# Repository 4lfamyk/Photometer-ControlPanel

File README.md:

# Raspberry-pi-photometer-controller
A control panel for photometer

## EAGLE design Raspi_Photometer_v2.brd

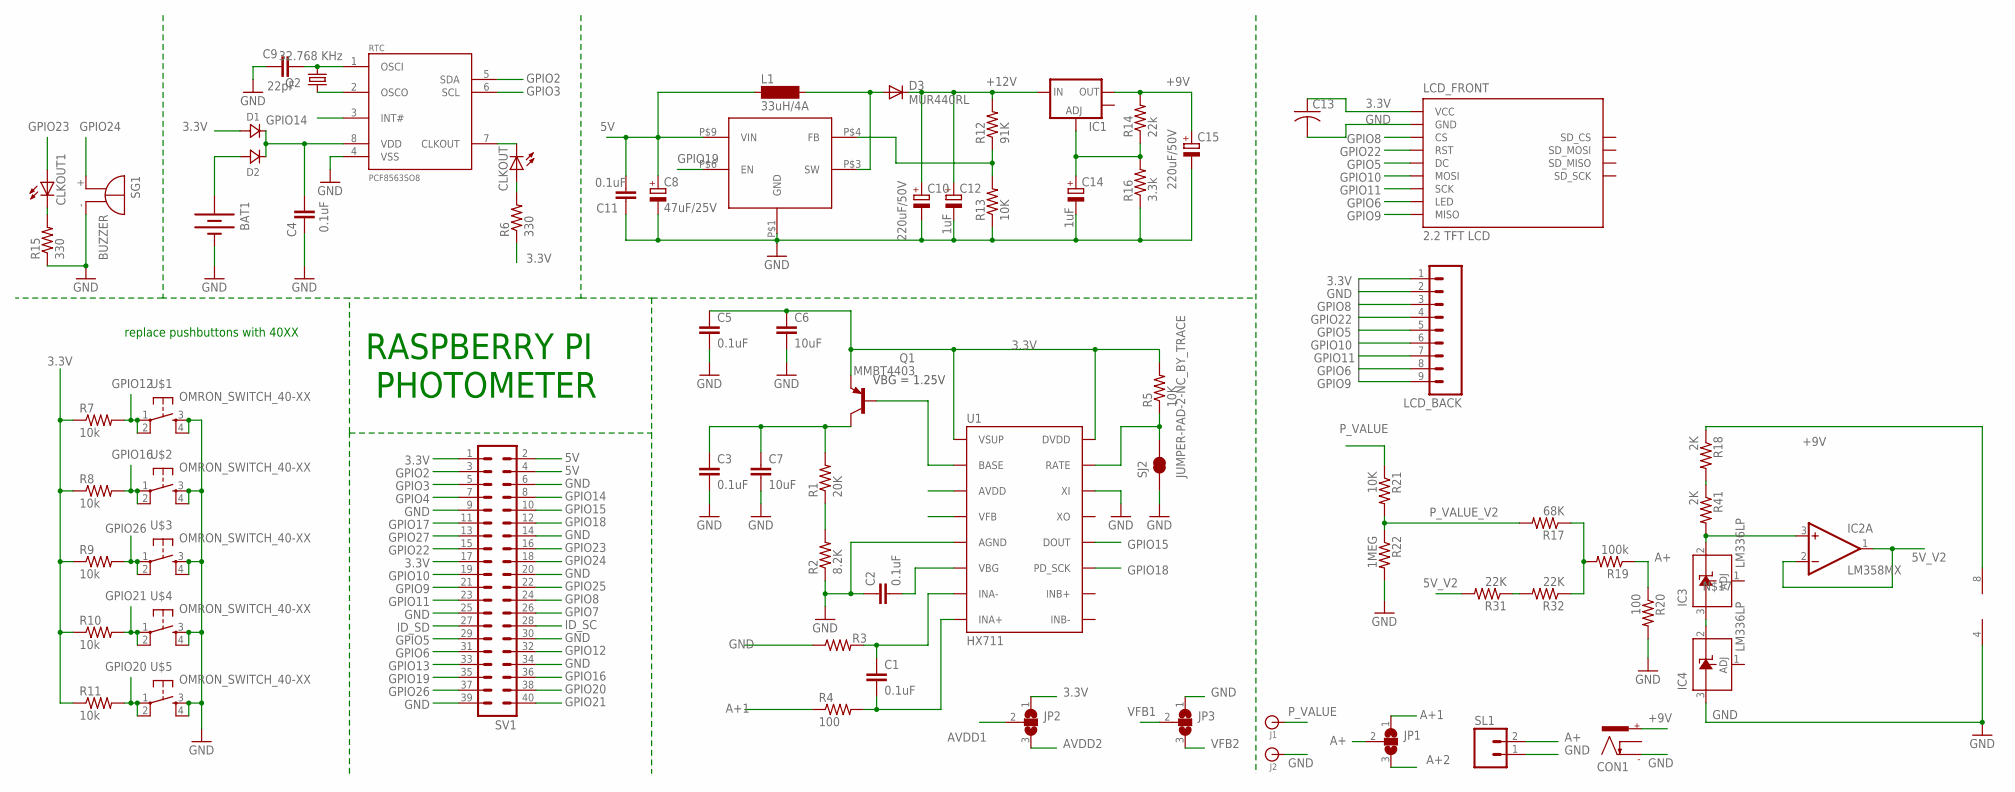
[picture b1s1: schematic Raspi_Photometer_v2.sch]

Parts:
BAT1: BATTERY20PTH; BATTCOM_20MM_PTH
C1, C2, C3, C5: 0.1uF; 0603-CAP
C4: 0.1uF; C0805K
C6, C7: 10uF; 1210
C8: 47uF/25V; E3,5-10
C9: 22pF; C0805K
C10, C15: 220uF/50V; E5-10,5
C11: 0.1uF; C0603
C12, C14: 1uF; E2,5-5
C13: C-USC0805; C0805
CLKOUT: LED0805; CHIPLED_0805
CLKOUT1: LED1206; CHIPLED_1206
CON1: POWER_CON; NEB21R
D1, D2: SS14; DO214
D3: MUR440RL; C2673
IC1: V_REG_LM1117SOT223; SOT223
IC2: LM358MX; SO08
IC3, IC4: LM336LP; TO92
J1, J2: BANANA_CONN
JP1, JP2, JP3: SJ2W; SJ_2
L1: 33uH/4A; MS85
LCD_BACK: M09; 09P
LCD_FRONT: TFT_LCD_2.2
Q1: MMBT4403; TO92-EBC
Q2: 32.768 KHz; TC26H
R1: 20K; 0204/7
R2: 8.2K; 0204/7
R3: 100; 0207/15
R4, R20: 100; 0207/7
R5, R13, R21: 10K; 0207/7
R6, R15: 330; 0204/7
R7, R8, R9, R10, R11: 10k; 0204/7
R12: 91K; 0207/7
R14: 22k; 0207/7
R16: 3.3k; 0207/7
R17: 68K; 0207/7
R18, R41: 2K; 0207/7
R19: 100k; 0207/7
R22: 1MEG; 0207/7
R31, R32: 22K; 0207/7
RTC: PCF8563SO8; SOIC8
SG1: BUZZER; F/TMB
SJ2: JUMPER-PAD-2-NC_BY_TRACE; PAD-JUMPER-2-NC_BY_TRACE_YES_SILK
SL1: M02; 02P
SV1: ML40
U1: HX711; SO16
U$1, U$2, U$3, U$4, U$5: OMRON_SWITCH_40-XX; B3F-40XX
U$6: XL6009; TO-263-5L

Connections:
3.3V: C5.1, C6.1, C13.1, D1.ANODE, JP2.1, LCD_BACK.1, LCD_FRONT.VCC, Q1.E, R5.2, R6.1, R7.1, R8.1, R9.1, R10.1, R11.1, SV1.1, SV1.17, U1.1 (VSUP), U1.16 (DVDD)
5V: C8.+, C11.2, L1.1, SV1.2, SV1.4, U$6.P$9 (VIN)
5V_V2: IC2.1 (OUT), IC2.2 (-IN), R31.2
+9V: C15.+, CON1.+, IC1.2 (OUT), IC2.8 (V+), R14.2, R18.1
+12V: C10.+, C12.+, D3.C, IC1.3 (IN), R12.2
A+: JP1.2, R19.1, R20.1, SL1.2
A+1: JP1.1, R4.1
A+2: JP1.3
AVDD1: JP2.2, U1.3 (AVDD)
AVDD2: C3.1, C7.1, JP2.3, Q1.C, R1.2
GND: BAT1.2 (-), C2.1, C3.2, C4.1, C5.2, C6.2, C7.2, C8.-, C9.1, C10.-, C11.1, C12.-, C13.2, C14.-, C15.-, CON1.-, IC2.4 (V-), IC4.3 (A), J2.P$2, JP3.1, LCD_BACK.2, LCD_FRONT.GND, R2.1, R3.1, R13.1, R15.1, R16.1, R20.2, R22.2, RTC.4 (VSS), SG1.-, SJ2.1, SL1.1, SV1.6, SV1.9, SV1.14, SV1.20, SV1.25, SV1.30, SV1.34, SV1.39, U1.5 (AGND), U1.14 (XI), U$1.3 (S), U$1.4 (S1), U$2.3 (S), U$2.4 (S1), U$3.3 (S), U$3.4 (S1), U$4.3 (S), U$4.4 (S1), U$5.3 (S), U$5.4 (S1), U$6.P$1 (GND)
GPIO2: RTC.5 (SDA), SV1.3
GPIO3: RTC.6 (SCL), SV1.5
GPIO4: SV1.7
GPIO5: LCD_BACK.5, LCD_FRONT.DC, SV1.29
GPIO6: LCD_BACK.8, LCD_FRONT.LED, SV1.31
GPIO7: SV1.26
GPIO8: LCD_BACK.3, LCD_FRONT.CS, SV1.24
GPIO9: LCD_BACK.9, LCD_FRONT.MISO, SV1.21
GPIO10: LCD_BACK.6, LCD_FRONT.MOSI, SV1.19
GPIO11: LCD_BACK.7, LCD_FRONT.SCK, SV1.23
GPIO12: R7.2, SV1.32, U$1.1, U$1.2 (P1)
GPIO13: SV1.33
GPIO14: RTC.3 (INT#), SV1.8
GPIO15: SV1.10, U1.12 (DOUT)
GPIO16: R8.2, SV1.36, U$2.1, U$2.2 (P1)
GPIO17: SV1.11
GPIO18: SV1.12, U1.11 (PD_SCK)
GPIO19: SV1.35, U$6.P$6 (EN)
GPIO20: R11.2, SV1.38, U$5.1, U$5.2 (P1)
GPIO21: R10.2, SV1.40, U$4.1, U$4.2 (P1)
GPIO22: LCD_BACK.4, LCD_FRONT.RST, SV1.15
GPIO23: CLKOUT1.A, SV1.16
GPIO24: SG1.+, SV1.18
GPIO25: SV1.22
GPIO26: R9.2, SV1.37, U$3.1, U$3.2 (P1)
GPIO27: SV1.13
ID_SC: SV1.28
ID_SD: SV1.27
unnamed: R5.1, SJ2.2, U1.15 (RATE)
unnamed: C1.1, R3.2, U1.7 (INA-)
unnamed: C1.2, R4.2, U1.8 (INA+)
unnamed: Q1.B, U1.2 (BASE)
unnamed: BAT1.1 (+), D2.ANODE
unnamed: R31.1, R32.2
unnamed: C2.2, U1.6 (VBG)
unnamed: C4.2, D1.CATHODE, D2.CATHODE, RTC.8 (VDD)
unnamed: CLKOUT.C, RTC.7 (CLKOUT)
unnamed: CLKOUT.A, R6.2
unnamed: C9.2, Q2.1, RTC.1 (OSCI)
unnamed: Q2.2, RTC.2 (OSCO)
unnamed: D3.A, L1.2, U$6.P$3 (SW)
unnamed: R12.1, R13.2, U$6.P$4 (FB)
unnamed: IC2.3 (+IN), IC3.2 (C), R41.2
unnamed: C14.+, IC1.1 (ADJ), R14.1, R16.2
unnamed: CLKOUT1.C, R15.2
unnamed: R17.1, R19.2, R32.1
unnamed: R18.2, R41.1
unnamed: IC3.3 (A), IC4.2 (C)
P_VALUE: J1.P$2, R21.1
P_VALUE_V2: R17.2, R21.2, R22.1
VFB1: JP3.2, U1.4 (VFB)
VFB2: JP3.3, R1.1, R2.2

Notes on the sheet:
VBG = 1.25V
RASPBERRY PI PHOTOMETER
replace pushbuttons with 40XX

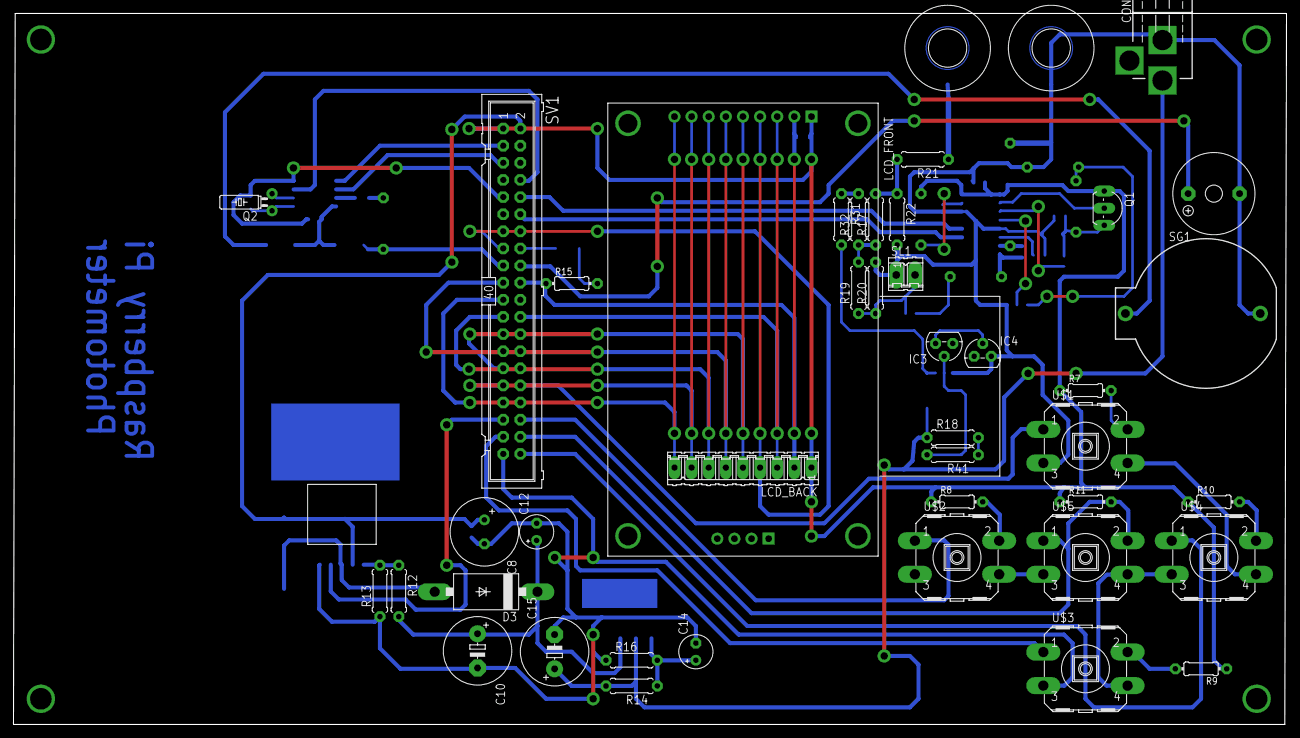
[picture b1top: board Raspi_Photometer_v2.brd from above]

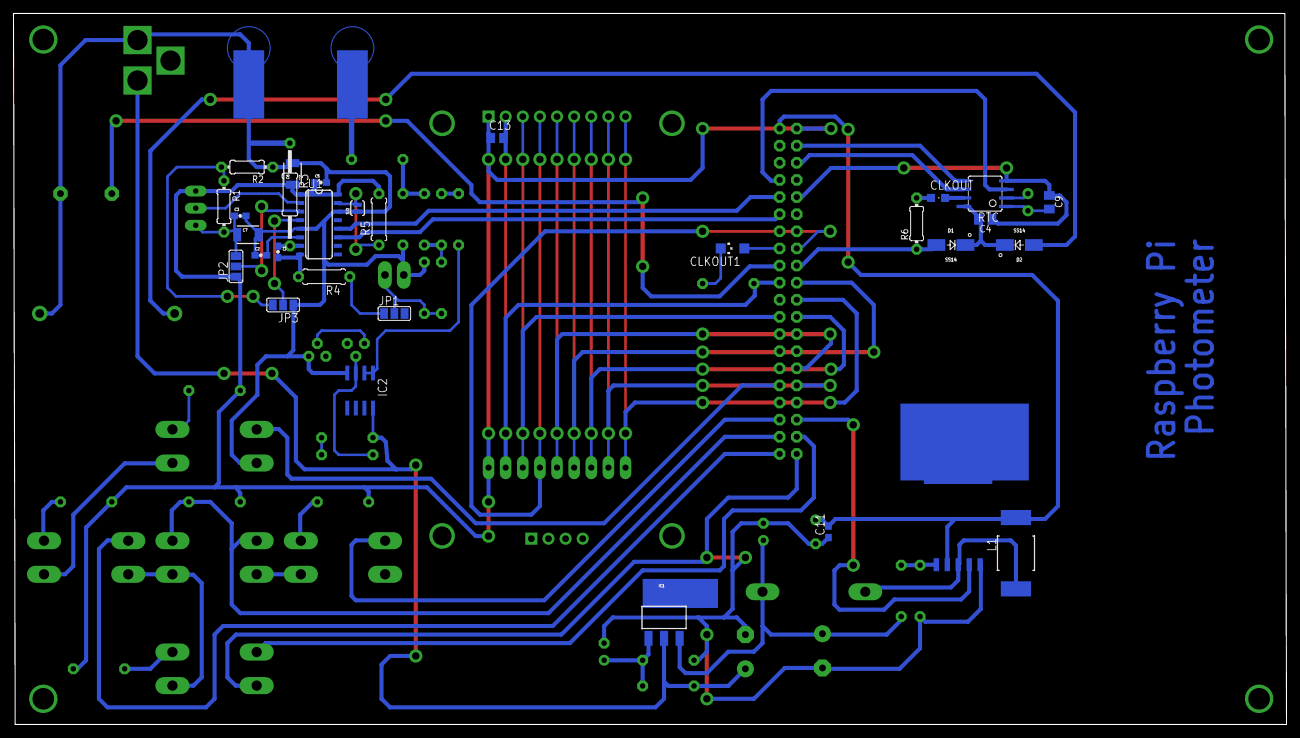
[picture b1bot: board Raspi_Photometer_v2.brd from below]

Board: 2 copper layers, 188.8 x 105.5 mm, 73 parts (29 on the bottom side), 54 nets.

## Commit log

2017-03-18 An initial version of the Raspberry Pi based photometer
2017-03-18 Addressed minimum value of sample spinbox
2017-03-20 Added some stuff
2017-03-21 Started integrations
2017-03-24 Incorporated sensor codes
2017-03-24 Merged controlThread and Main Thread
2017-03-25 Implemented Control Logic
2017-03-27 inserted pin mapping
2017-03-29 Photometer application under test

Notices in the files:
parts and their libraries:
SparkFun-Capacitors: Licensing: Creative Commons ShareAlike 4.0 International - https://creativecommons.org/licenses/by-sa/4.0
SparkFun-Aesthetics: Licensing: CC v3.0 Share-Alike You are welcome to use this library for commercial purposes.
